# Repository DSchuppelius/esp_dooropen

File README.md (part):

# esp_dooropen

SIP-Türöffner für **ESP32 DevKit (WROOM-32)**, **WT32-ETH01** (ESP32 mit Ethernet) oder
**ESP8266 HW-364A** (NodeMCU mit fest verbautem OLED). Klingelt es, ruft der ESP per SIP ein Telefon an; mit **`*`** (oder einem Code) am
Telefon, über die **Weboberfläche**, per **Taster** oder aus **Home Assistant** wird die
Tür geöffnet.

Die Zielplattform wird über die PlatformIO-Umgebung gewählt (siehe
[Bauen & Flashen](#bauen--flashen-platformio)); der Code passt sich per
Präprozessor-Weiche automatisch an.

## Funktionen

- **Klingel-Eingang** (potentialfreier Kontakt, entprellt) mit Zähler und Hinweis
  „Es klingelt!“ im Web, auf dem Display und in Home Assistant.
- **Türsummer** über ein Relais, Dauer einstellbar (1–30 s). Ein Hardware-Timer
  schaltet das Relais auch dann pünktlich ab, wenn das Programm gerade hängt.
- **SIP-Anruf beim Klingeln** (getestet mit Asterisk, REGISTER mit Digest-Auth
  inkl. `qop=auth`/`opaque`, auch LANCOM-kompatibel):
  - **Rufkette**: mehrere Nummern nacheinander (z. B. `100, 101`), bis jemand abhebt,
  - nach dem Abheben ein Piepton im Hörer (G.711 A-law/µ-law), danach ein kurzer
    Piep alle 3 s, solange die Leitung offen ist,
  - **`*` am Telefon** (DTMF per RFC 4733 oder SIP INFO) öffnet die Tür und legt auf –
    oder ein **Öffnen-Code** (z. B. `1234`); dafür bleibt das Gespräch 30 s offen,
  - wird nicht abgehoben, wird der Anruf nach 15 s per `CANCEL` zurückgezogen,
  - **SIP-Status im Klartext** und Ergebnis des letzten Anrufs,
  - **robust im WLAN**: `INVITE` (auch mit Digest), `CANCEL`, `BYE` und `REGISTER`
    werden bei Paketverlust wiederholt (RFC 3261); eine gescheiterte Erneuerung
    meldet erst „abgemeldet“, wenn die Anmeldung wirklich abläuft. Kopfzeilen in
    jeder Schreibweise und Kurzform (`i:`, `f:` …) werden verstanden; ein Server als
    Hostname wird einmal je Anmeldung aufgelöst (folgt auch einem DHCP-Wechsel).
- **Klingeln per Anruf**: Eine TK-Anlage (z. B. OpenCom) ruft beim Klingeln den
  Türöffner an – er nimmt nicht ab und wertet das als Klingeln. Ganz ohne Verdrahtung.
- **Anrufe an den Türöffner** (optional): Wer die Nebenstelle des Türöffners anruft,
  hört einen kurzen Ton und tippt den Öffnen-Code oder einen **Gästecode**
  (bis zu 5, mit Name, Ablaufdatum und „einmalig“). Nach mehreren falschen Codes
  werden Anrufe für 15 min gesperrt.
- **Weboberfläche** mit hellem/dunklem Design, großem Öffnen-Knopf mit
  Countdown-Ring, Statuskacheln, Test-Anruf und Ton-Benachrichtigung im Browser.
- **Home Assistant** per MQTT mit Auto-Discovery (Schloss, Button, Klingel-Ereignis,
  Sensoren, letztes Ereignis, Einstellungen).
- **OLED SSD1306** (optional) zeigt IP, Signal- und Summer-Status; wird kein
  Display gefunden, läuft alles ohne.
- **Status-LED** mit Blinkmustern (Summer, WLAN-Einrichtung, kein WLAN, SIP fehlt).
- **Taster** vor Ort: Klingel-Taster (wirkt wie Klingeln) und Summer-Taster (öffnet).
- **Zweites Relais** (Tor, Garage, zweite Tür) mit eigenem Knopf, eigener Dauer und
  wahlweise auch für den Tür-Zugang.
- **Tastenfeld / RFID-Leser** (Wiegand, ESP32): Öffnen-Code oder Gästecode am
  Tastenfeld, Karten/Chips mit Namen; Sperre nach Fehlversuchen.
- **Telegram-Bot** (ESP32): Klingel-Mitteilung mit Knopf **„Öffnen“**, Befehle
  `/status` und `/oeffnen` – auch unterwegs, ohne Portfreigabe.
- **Apple Home** (HomeKit, eigene ESP32-Variante): Türschloss mit Türklingel direkt in
  der Home-App, ohne Home Assistant.
- **Zugänge** mit eigener Anmeldeseite: Admin (alles) und Tür-Zugang (nur öffnen und
  Verlauf sehen, z. B. für den Kunden; ohne Tür-Passwort ist die Tür offen), dazu bis
  zu 8 **weitere Benutzer** mit Rolle und Zeitfenster – der Verlauf zeigt, wer
  geöffnet hat. Ohne Admin-Passwort warnt die Oberfläche deutlich.
- **Firmware-Update über WLAN**: per Browser-Upload oder aus PlatformIO (OTA, nur
  mit Admin-Passwort).
- **Erreichbar unter `http://tueroeffner.local`** (mDNS).
- **Verlauf** der letzten 30 Ereignisse mit Uhrzeit (NTP) und Detail (z. B. Name des
  Gästecodes, Nummer des Anrufers, Benutzer); **übersteht Neustarts**. Dazu ein langer
  Verlauf (mehrere Tausend Einträge) im Flash, als **CSV** herunterladbar.
- **Nachtruhe**: in einem Zeitfenster beim Klingeln nicht anrufen.
- **Praxis-Modus**: an gewählten Wochentagen in **zwei Zeitfenstern** öffnet Klingeln
  die Tür automatisch (ohne Anruf); **gesetzliche Feiertage je Bundesland** werden
  automatisch berücksichtigt, weitere **Ausnahmetage** (Urlaub) einstellbar. Bei
  Fenstern über Mitternacht (z. B. 22–2 Uhr) gehört der Teil nach Mitternacht zum
  Vortag (Wochentag, Feier- und Ausnahmetag des Vortags).
- **Uhrzeit** per NTP: `pool.ntp.org`, ersatzweise das **Gateway** (Router oder
  TK-Anlage, z. B. FRITZ!Box „Zeitserver im Heimnetz bereitstellen“) und
  `de.pool.ntp.org`. So laufen Praxis-Modus, Nachtruhe und Zeitfenster auch ohne
  Internet, wenn der Router NTP anbietet. Ohne gültige Uhrzeit sind Praxis-Modus und
  Nachtruhe aus.
- **Türkontakt** (Reed): Tür offen/zu im Web und in Home Assistant, Meldung, wenn die
  Tür zu lange offen steht, und Prüfung, ob nach dem Summer wirklich jemand
  hereinkam („Tür nach Summer geöffnet“ / „Summer, Tür blieb zu“).
- **Push-Mitteilungen ohne Home Assistant** über **ntfy** oder **Telegram**
  (Klingeln, Öffnen, Tür zu lange offen, Sperre nach falschen Codes).
- **Syslog**: Meldungen und Ereignisse an einen Syslog-Server (Fehlersuche aus der Ferne).
- **Ethernet** statt WLAN mit dem WT32-ETH01 (z. B. per PoE versorgt).
- **Selbstheilung**: Ist das WLAN weg, verbindet der ESP jede Minute neu; als letzte
  Stufe Neustart nach 30 min. Ethernet: Neustart nur, wenn ein Link da ist, aber
  10 min keine IP kommt (bei gezogenem Kabel nicht). Außerdem Neustart, wenn der
  Speicher knapp oder zerstückelt ist oder das Programm hängt (Watchdog auf beiden
  Boards); der Grund des letzten Starts wird angezeigt.
- **Neue IP per DHCP** wird erkannt, SIP meldet sich dann sofort neu an.
- **Sicherung**: alle Einstellungen als Datei herunterladen und wieder einspielen.
- **Feste IP-Adresse** wahlweise statt DHCP (vor dem Speichern geprüft: Maske,
  Gateway im selben Netz, keine Netz-/Broadcast-Adresse – gegen Aussperren).
- **Sperre gegen Sturmklingeln**: Klingeln innerhalb von 5 s löst keinen neuen
  Anruf aus.
- **WiFiManager**: Ohne gespeicherte Zugangsdaten öffnet der ESP das
  passwortgeschützte WLAN `Tueroeffner-Setup` zum Eintragen – **ohne zu blockieren**:
  Klingel, Taster und Summer funktionieren währenddessen weiter. Ist das bekannte WLAN
  nur weg (z. B. startet der Router nach einem Stromausfall langsamer als der ESP),
  verbindet er weiter und öffnet die Einrichtung erst nach 15 min ohne Verbindung –
  dann für 5 min, während die Verbindung zum WLAN weiter versucht wird.
- Einstellungen, Zähler und Verlauf liegen im **LittleFS** (Zähler/Verlauf werden
  höchstens alle 5 min geschrieben, der lange Verlauf gebündelt höchstens einmal pro
  Minute, um den Flash zu schonen; vor Neustart und Update wird alles gesichert).
  Gespeichert wird geprüft über eine Hilfsdatei – bei vollem oder defektem Speicher
  bleibt die alte Datei, die Oberfläche meldet den Fehler. Für die Einstellungen bleibt
  immer Platz frei (notfalls wird der ältere Verlauf gelöscht). Wurde der Speicher beim
  Start formatiert oder ist er nicht verfügbar, zeigt die Oberfläche eine Warnung.
  Ereignisse ohne Uhrzeit (kein NTP) bleiben erhalten und erscheinen als „ohne Uhrzeit“.

## Verdrahtung

### ESP32 DevKit (WROOM-32)

Hier gelten echte GPIO-Nummern. Ein OLED ist optional.

| Funktion             | Pin      | Hinweis                                  |
|----------------------|----------|------------------------------------------|
| Relais S (Signal)    | GPIO26   | schaltet das Relais (active-high)        |
| Relais + / -         | 5V / GND | Relais-Modul aus 5 V versorgen           |
| Klingel-Kontakt      | GPIO27   | eine Ader hier, andere Ader an GND       |
| Klingel-Taster       | GPIO32   | Taster gegen GND, wirkt wie Klingeln     |
| Summer-Taster        | GPIO33   | Taster gegen GND, öffnet die Tür         |
| Türkontakt (optional)| GPIO25   | Reed-Kontakt gegen GND, geschlossen = zu |
| Status-LED           | GPIO2    | onboard oder extern, siehe [Status-LED](#status-led) |
| OLED SDA (optional)  | GPIO21   | nur falls ein Display genutzt wird       |
| OLED SCL (optional)  | GPIO22   | nur falls ein Display genutzt wird       |
| Relais 2 (optional)  | GPIO13   | zweites Relais (Tor, Garage …)           |
| Wiegand D0 (optional)| GPIO18   | Tastenfeld/RFID-Leser, siehe unten       |
| Wiegand D1 (optional)| GPIO19   | Tastenfeld/RFID-Leser, siehe unten       |

### ESP8266 HW-364A

Das OLED ist auf dem HW-364A **fest verdrahtet** an D5/D6.

| Funktion            | Pin         | Hinweis                                  |
|---------------------|-------------|------------------------------------------|
| OLED SDA (onboard)  | D5 (GPIO14) | fest verbaut, nicht belegen              |
| OLED SCL (onboard)  | D6 (GPIO12) | fest verbaut, nicht belegen              |
| KY-019 S (Signal)   | D1 (GPIO5)  | schaltet das Relais (active-high)        |
| KY-019 + (VCC)      | 5V / VU     | 5 V vom USB-Pin (nicht 3V3!)             |
| KY-019 - (GND)      | G           | gemeinsame Masse                         |
| Klingel-Kontakt     | D2 (GPIO4)  | eine Ader hier, andere Ader an GND       |
| Klingel-Taster      | D7 (GPIO13) | Taster gegen GND, wirkt wie Klingeln     |
| Summer-Taster       | D3 (GPIO0)  | gegen GND; Boot-Pin, nicht beim Start    |
| Türkontakt (opt.)   | RX (GPIO3)  | Reed gegen GND; beim USB-Flashen offen   |
| Relais 2 (opt.)     | D0 (GPIO16) | zweites Relais (Tor, Garage …)           |

Tastenfeld/RFID (Wiegand) gibt es auf dem ESP8266 nicht – dafür sind keine Pins frei.

**Summer-Taster an D3 (GPIO0):** GPIO0 entscheidet beim Start, ob der ESP8266 normal
startet oder auf eine neue Firmware wartet. Ist der Taster beim Einschalten **oder bei
einem Neustart** (Update, Selbstheilung, Watchdog) gedrückt – oder klemmt er bzw. ist
die Leitung feucht –, bleibt der ESP im Flash-Modus hängen, bis er stromlos war. Die
Firmware kann das nicht abfangen. Für Dauerbetrieb daher ESP32 bzw. die Steuerplatine
nutzen oder den Taster so montieren, dass er nicht klemmen kann.

### WT32-ETH01 (Ethernet)

Umgebung `wt32-eth01`. Netzwerk über das eingebaute LAN8720 (kein WLAN, keine
WLAN-Einrichtung; feste IP wie gewohnt in der Weboberfläche). IO35/IO36/IO39 sind
reine Eingänge **ohne** internen Pull-up.

| Funktion             | Pin   | Hinweis                                       |
|----------------------|-------|-----------------------------------------------|
| Relais (Summer)      | IO4   | active-high                                   |
| Klingel-Kontakt      | IO32  | gegen GND                                     |
| Klingel-Taster       | IO33  | gegen GND                                     |
| Summer-Taster        | IO12  | gegen GND (Strapping-Pin: nie auf 3,3 V ziehen) |
| Türkontakt           | IO2   | gegen GND                                     |
| Status-LED           | IO17  | LED mit 330 Ω gegen GND                        |
| Relais 2             | IO5   | Strapping-Pin, siehe Relais beim Start        |
| Wiegand D0 / D1      | IO35 / IO36 | Pull-up bzw. Pegelwandler nötig         |
| OLED SDA / SCL       | IO15 / IO14 | optional                                |

### Relais beim Start

Die Firmware setzt die Relais als allererstes in Ruhelage. Davor – während Reset,
Bootloader und Programmstart (einige 100 ms) – bestimmt die Hardware den Pegel:

| Board | Relais 2 | Pegel beim Start | Risiko |
| --- | --- | --- | --- |
| ESP32 DevKit / [Steuerplatine](hardware/README.md) | GPIO13 | kein Pull-up | keins (Platine: 100 kΩ hält das Gate auf GND) |
| WT32-ETH01 | IO5 | interner **Pull-up** (Strapping-Pin) | active-high-Modul kann kurz anziehen |
| ESP8266 | D0 (GPIO16) | beim Start **HIGH** | active-high-Modul kann kurz anziehen |

Relais 1 (Summer: GPIO26, IO4, D1/GPIO5) ist davon nicht betroffen. Hängt an Relais 2
etwas, das schon ein kurzer Impuls auslöst (Tor, Garage):

- **WT32-ETH01:** einen **Pull-down von 4,7–10 kΩ** vom Relais-Eingang (IN/S) nach GND
  einbauen – stärker als der interne Pull-up; IO5 darf beim Start LOW sein (betrifft
  nur das SDIO-Timing).
- **WT32-ETH01 und ESP8266:** ein Relais-Modul nehmen, das bei **LOW** schaltet, und in
  [src/config.h](src/config.h) `RELAY2_ACTIVE_LOW` auf `true` setzen – der HIGH-Pegel
  beim Start bedeutet dann „aus“.

### Tastenfeld / RFID-Leser (Wiegand)

Viele Zutritts-Tastenfelder und Kartenleser haben eine **Wiegand-Schnittstelle**
(Leitungen D0, D1, GND). Erkannt werden Tastendrücke (4 bzw. 8 Bit) und Karten
(26 Bit mit Parität, 34 Bit).

```text
Leser D0 (grün) ──[Pegelwandler]── GPIO18     Leser GND ── GND
Leser D1 (weiß) ──[Pegelwandler]── GPIO19     Leser +12 V ── eigenes Netzteil
```

Die meisten Leser ziehen D0/D1 auf **5 V** hoch – das verträgt der ESP32 nicht. Dann
einen **Pegelwandler** (z. B. BSS138-Modul) oder je Leitung einen Spannungsteiler
(z. B. 10 kΩ / 20 kΩ) dazwischen. Leser mit Open-Collector-Ausgang können direkt an
die Pins (der ESP schaltet den internen Pull-up ein).

Bedienung am Tastenfeld: Code eintippen, **#** bestätigt, ***** löscht. Gültig sind
Öffnen-Code und Gästecodes. Karten werden unter **Einstellungen → Tastenfeld / RFID**
angelernt: Karte an den Leser halten, die Nummer erscheint dort zum Übernehmen.

### Türöffner und Klingel

Der Türöffner hängt am **Relaiskontakt** (COM + NO) zusammen mit einem
**Klingeltrafo** (8–12 V AC): Trafo → COM, NO → Türöffner → zurück zum Trafo.

**Wichtig:**

- Der **Klingel-Eingang** verträgt nur einen *potentialfreien Kontakt* oder einen
  Optokoppler-Ausgang – **niemals die Klingelspannung direkt** (siehe
  [Klingel-Eingang anschließen](#klingel-eingang-anschließen)).
- Der **Summer** wird **nicht** vom ESP versorgt. Der ESP schaltet nur das Relais,
  der Summer hat seinen eigenen Stromkreis.
- Die Voreinstellung passt für das **KY-019** (schaltet bei HIGH). Für Relais-Module,
  die bei LOW schalten (viele blaue Module), in `src/config.h`
  `RELAY_ACTIVE_LOW` auf `true` setzen.

- **Zusätzliche Absicherung (empfohlen):** Das Relais wird per Hardware-Timer
  abgeschaltet, auch wenn das Programm hängt. Gegen einen *Defekt* des ESP (Pin bleibt
  auf HIGH) hilft das nicht. Wer das ausschließen will, schaltet den Türöffner über ein
  **Zeitrelais/Monoflop** (z. B. NE555-Schaltung oder fertiges „Delay Off“-Modul mit
  max. 30 s), das der ESP nur anstößt.

### Klingel-Eingang anschließen

Der Klingel-Eingang (ESP32: **GPIO27**, ESP8266: **D2**) arbeitet mit internem Pull-up:
**aktiv = gegen GND gezogen**. Erkannt werden sowohl Dauersignale als auch mit 50 Hz
pulsierende Signale (Optokoppler an Wechselspannung) – das Signal gilt als aktiv,
solange es in den letzten 40 ms aktiv war (`SIGNAL_AC_HOLD_MS`).

Gegen Störungen: Das Signal allein braucht mindestens 3 aktive Abtastungen
(`SIGNAL_MIN_SAMPLES`), und solange der Summer an ist sowie 300 ms danach zählt
Klingeln nicht (`RING_BUZZER_GUARD_MS`, Einkopplung vom Türöffner). Ein Eingang, der
schon beim Start aktiv ist (klemmender Taster, Feuchte), zählt erst, nachdem er einmal
frei war – das gilt auch für den Summer-Taster. Hängt das Programm kurz (Netzwerk,
Flash), erkennt ein Interrupt Tastendrücke ab 50 ms trotzdem und holt sie nach.

Welche Variante passt?

| Was ist vorhanden? | Variante |
| --- | --- |
| freier Schaltkontakt (Relaisausgang einer Sprechanlage, zweiter Kontakt am Taster) | **A** – direkt |
| klassische Klingel mit Klingeltrafo (8–12 V~) und Gong | **B** – Optokoppler parallel zum Gong |
| Klingeltaster an einer **TK-Anlage** (Sensor-Eingang, z. B. Aastra/Mitel OpenCom) | **C** – Optokoppler parallel zum Sensor |
| Klingel mit Gleichspannung (z. B. 12 V⎓) | **D** – Optokoppler, Polung beachten |
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
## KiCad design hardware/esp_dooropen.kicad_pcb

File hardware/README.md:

# Steuerplatine (KiCad)

KiCad-10-Projekt für eine eigene Platine mit ESP32-WROOM-32E. Die Pinbelegung entspricht dem ESP32-Zweig in [src/config.h](../src/config.h), es ist also keine Firmware-Änderung nötig.

| Datei | Inhalt |
| --- | --- |
| `esp_dooropen.kicad_pro` / `.kicad_sch` | KiCad-Projekt und Schaltplan |
| `schaltplan.pdf` | Schaltplan als PDF |
| `stueckliste.csv` | Stückliste, gruppiert nach Wert und Footprint |

Stand: nur der Schaltplan. Ein PCB-Layout gibt es noch nicht.

## Funktionsblöcke

- **Versorgung:** 12 V DC über Hohlstecker 5,5/2,1 oder Schraubklemme. Danach PTC 1,1 A, Verpolschutz SS34 und TVS-Diode SMBJ15CA. Ein RECOM R-78E5.0-1.0 erzeugt 5 V, ein AMS1117 daraus 3,3 V. USB-5V ist über eine Schottky-Diode entkoppelt, sodass USB und 12 V gleichzeitig angeschlossen sein dürfen.
- **USB-C:** CH340C mit Auto-Reset über DTR/RTS. Geflasht wird direkt per PlatformIO, ohne Tasten zu drücken. RESET und BOOT gibt es trotzdem als Taster.
- **Relais 1 und 2:** SRD-12VDC-SL-C mit 12-V-Spule, angesteuert über AO3400A mit Freilaufdiode und LED. Die Kontakte NO/COM/NC sind potentialfrei auf Schraubklemmen geführt.
- **Klingelsignal:** Zwei Varianten, beide verdrahtet. Sie wirken als ODER auf GPIO27 und brauchen keine Jumper.
  - Potentialfreier Kontakt an J4, Klemme 1 gegen GND.
  - 8–24 V AC oder DC an J5 über den Optokoppler LTV-814 (PC814). Der Optokoppler hat antiparallele LEDs, die Polarität ist also egal, und er trennt galvanisch. C11 überbrückt die Nulldurchgänge bei Wechselspannung.
- **Taster und Türkontakt:** Je 1 kΩ in Serie, 10 kΩ Pull-up und 100 nF gegen Störungen auf langen Leitungen.
- **Wiegand:** 12-V-Versorgung über PTC 200 mA. D0/D1 laufen über Schottky-Dioden BAT54W, daher sind 5-V-Leser ohne Pegelwandler erlaubt.
- **Erweiterungen:** OLED-Steckplatz (I2C, 3,3 V) und eine Erweiterungsleiste mit IO4, IO14, IO16 und IO17.

## Klemmenbelegung

| Klemme | Pins |
| --- | --- |
| J2 12 V | 1 +12 V, 2 GND |
| J4 Eingänge | 1 Klingel potentialfrei, 2 GND, 3 Klingeltaster, 4 Summertaster, 5 Türkontakt, 6 GND |
| J5 Klingel AC/DC | 1, 2 (8–24 V, beliebige Polarität) |
| J6 Wiegand | 1 +12 V, 2 GND, 3 D0, 4 D1 |
| J9 / J10 Relais | 1 NO, 2 COM, 3 NC |

## Zuordnung der GPIOs

| GPIO | Funktion |
| --- | --- |
| 26 | Relais 1 (Türsummer) |
| 13 | Relais 2 |
| 27 | Klingelsignal |
| 32 | Klingeltaster |
| 33 | Summertaster |
| 25 | Türkontakt |
| 18 / 19 | Wiegand D0 / D1 |
| 21 / 22 | I2C SDA / SCL |
| 2 | Status-LED |

## Hinweise

- **ERC:** Die einzige Meldung lautet „Power output an Power output“ zwischen CH340C-V3 und AMS1117. Das ist gewollt: Laut Datenblatt wird V3 bei 3,3-V-Betrieb mit VCC verbunden.
- **Nur Kleinspannung:** Die Platine ist für Kleinspannung ausgelegt (Klingeltrafo, Türöffner 8–24 V). Für 230 V an den Relaiskontakten fehlen die nötigen Luft- und Kriechstrecken.
- **Antenne:** Beim Layout muss die Antenne des WROOM-Moduls über den Platinenrand ragen. Darunter dürfen weder Kupfer noch Bauteile liegen.
- **Strapping-Pins:** GPIO12, GPIO15 und GPIO5 sind bewusst frei. GPIO0 und EN werden nur vom Auto-Reset und den Tastern benutzt.
- **Relais beim Start:** Die Relais hängen an GPIO26 und GPIO13 (keine Strapping-Pins, kein Pull-up beim Reset). R23 bzw. R25 (100 kΩ) halten die Gates von Q3/Q4 auf GND, solange der ESP32 startet – die Relais ziehen dabei nicht an. Bei Änderungen die Relais nicht auf GPIO5 oder GPIO15 legen (interner Pull-up beim Reset, siehe [README](../README.md#relais-beim-start)); diese Pull-downs nicht weglassen.

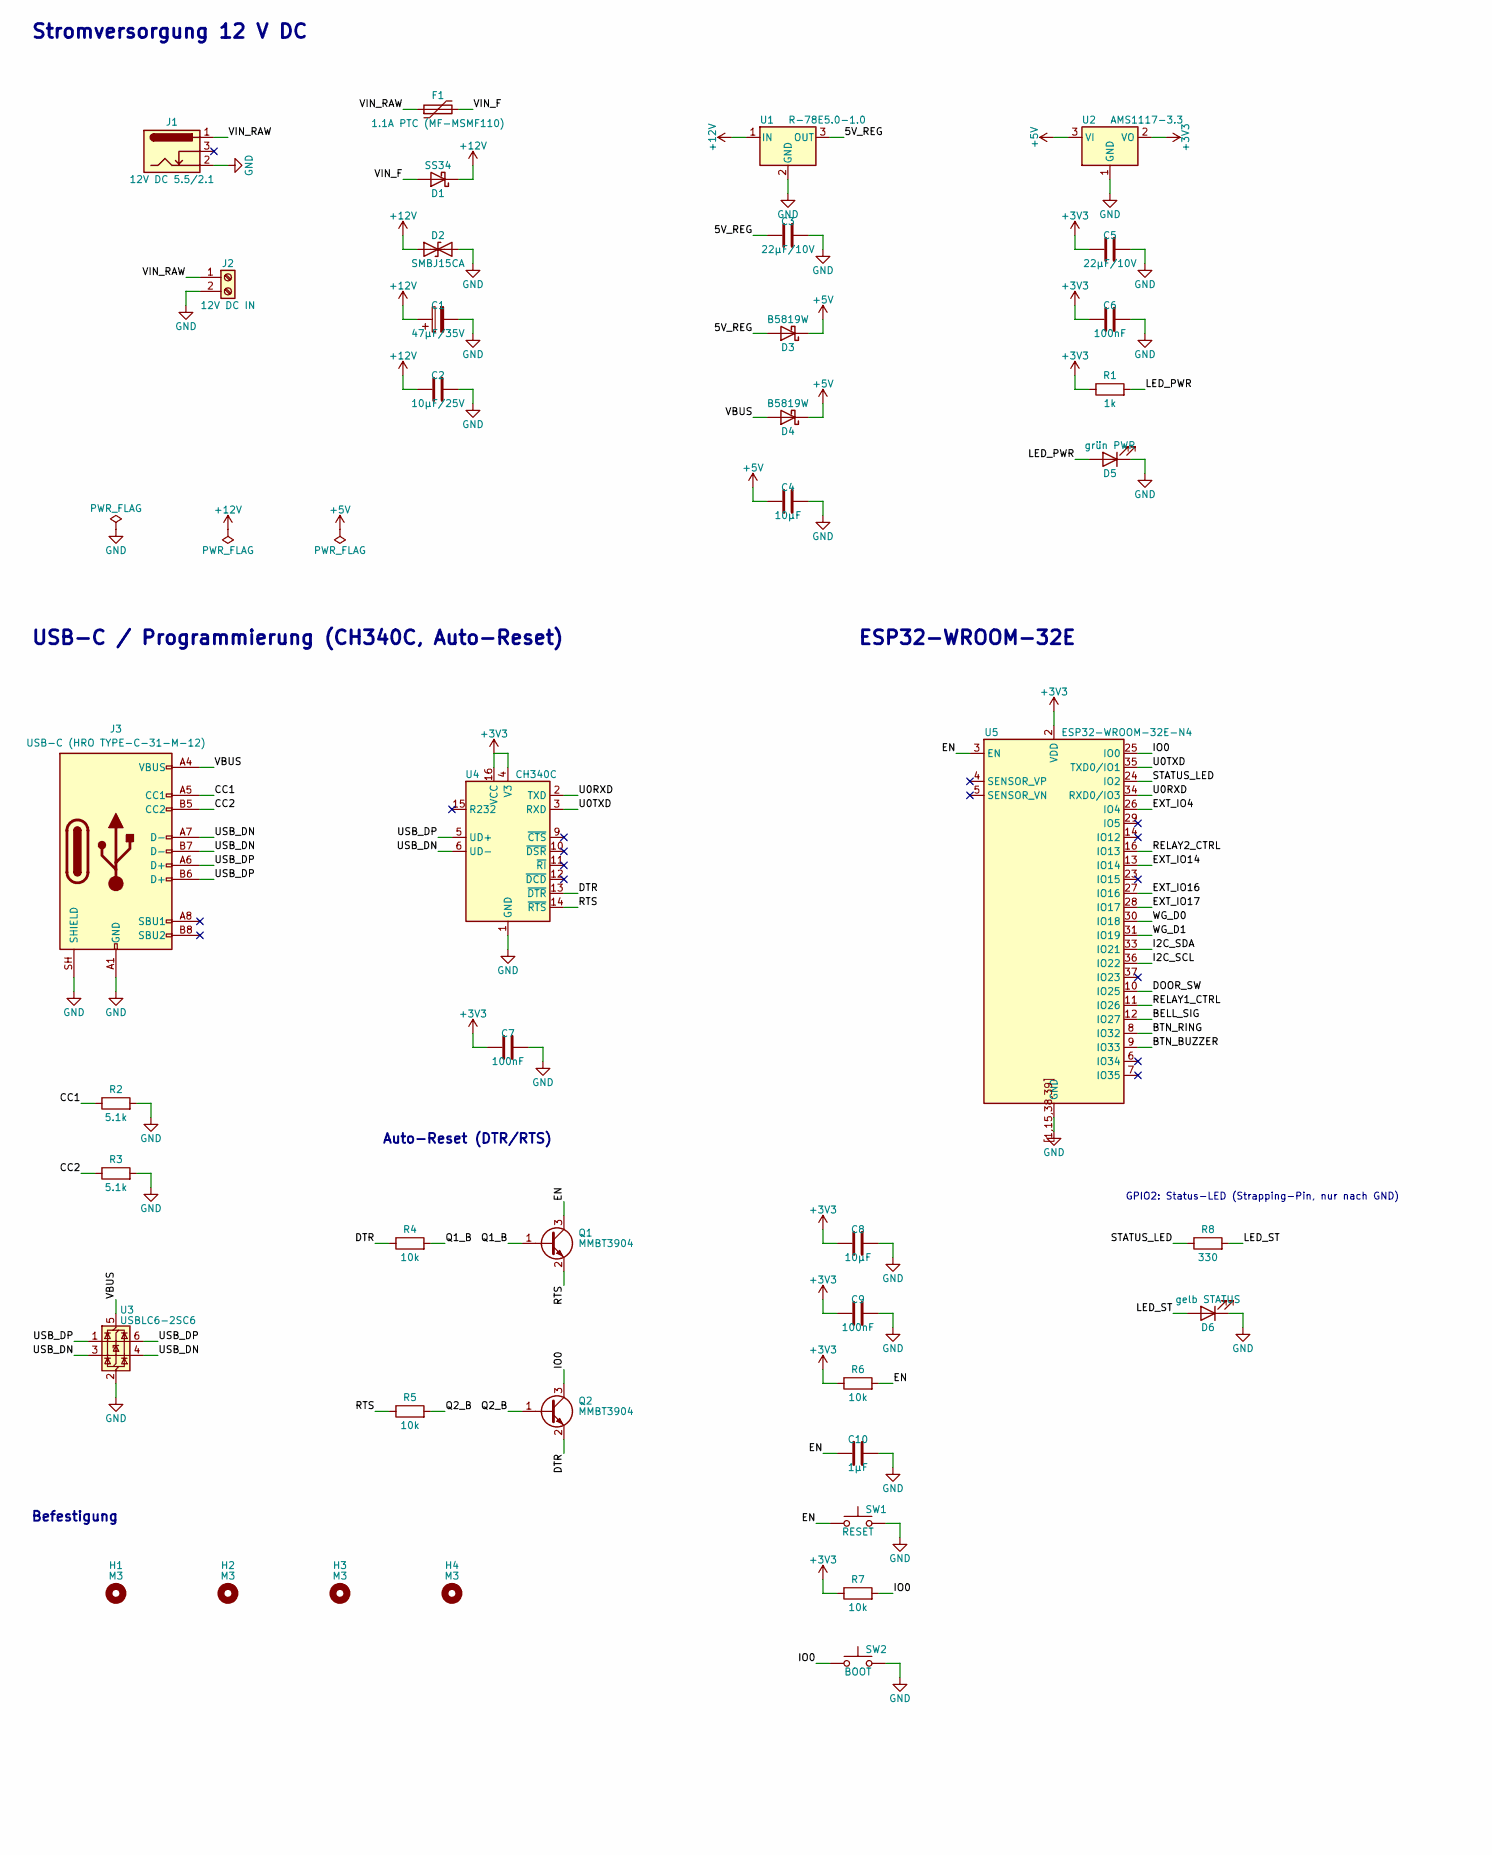
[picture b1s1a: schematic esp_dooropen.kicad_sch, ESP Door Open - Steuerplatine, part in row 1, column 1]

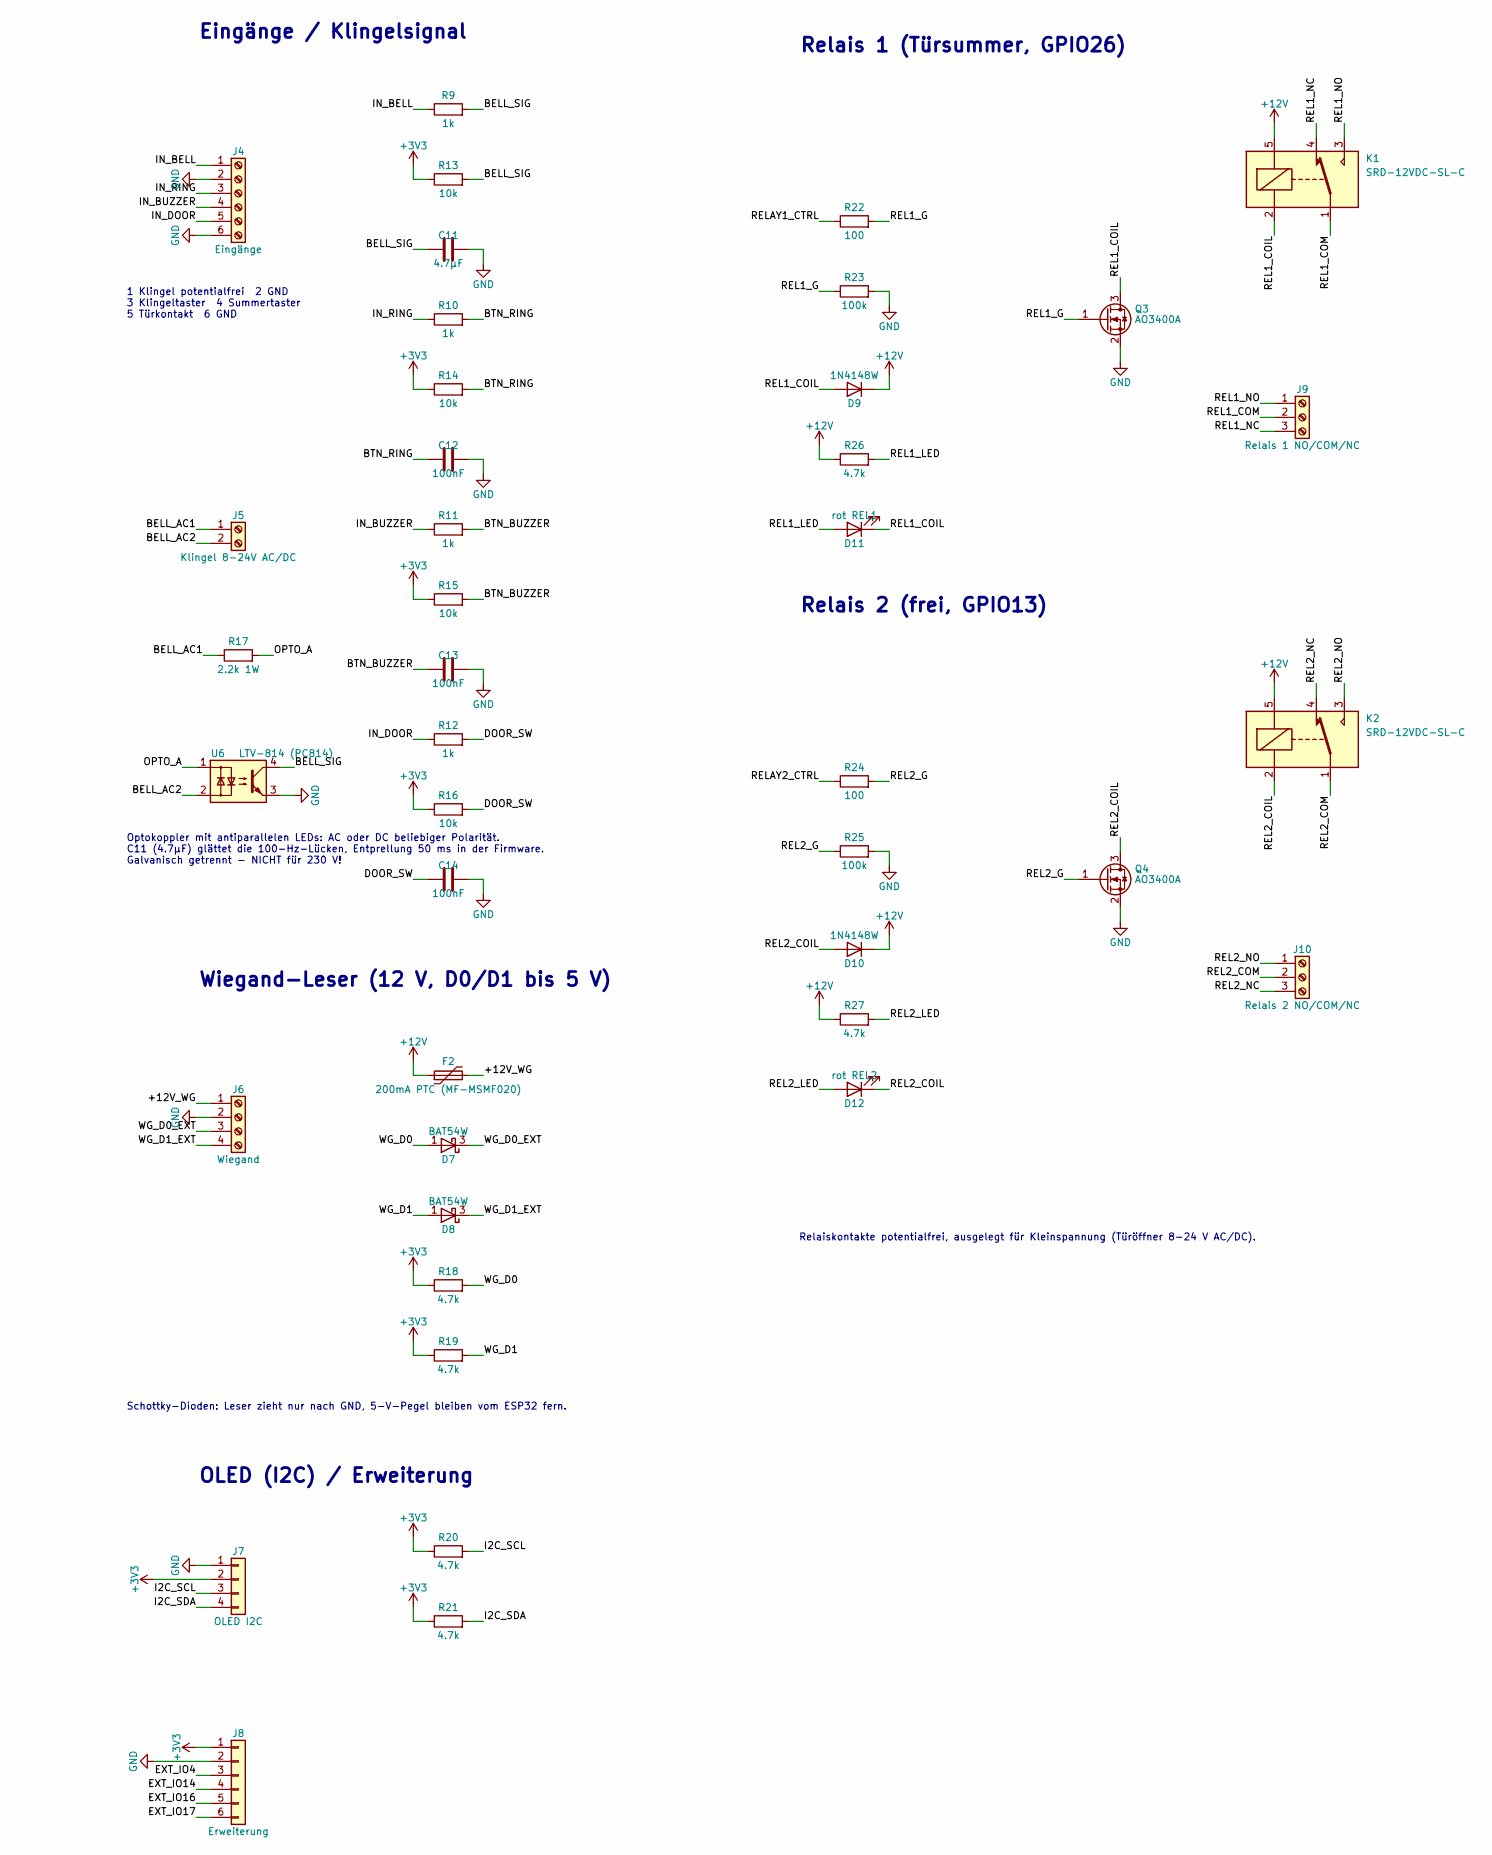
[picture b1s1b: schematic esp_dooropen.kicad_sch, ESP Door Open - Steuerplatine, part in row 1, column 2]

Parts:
C1: 47µF/35V; CP_Elec_6.3x7.7
C2: 10µF/25V; C_1206_3216Metric
C3, C5: 22µF/10V; C_1206_3216Metric
C4, C8: 10µF; C_0805_2012Metric
C6, C7, C9, C12, C13, C14: 100nF; C_0805_2012Metric
C10: 1µF; C_0805_2012Metric
C11: 4.7µF; C_0805_2012Metric
D1: SS34; D_SMA
D2: SMBJ15CA; D_SMB
D3, D4: B5819W; D_SOD-123
D5: grün PWR; LED_0805_2012Metric
D6: gelb STATUS; LED_0805_2012Metric
D7, D8: BAT54W; SOT-323_SC-70
D9, D10: 1N4148W; D_SOD-123
D11: rot REL1; LED_0805_2012Metric
D12: rot REL2; LED_0805_2012Metric
F1: 1.1A PTC (MF-MSMF110); Fuse_1812_4532Metric
F2: 200mA PTC (MF-MSMF020); Fuse_1206_3216Metric
H1, H2, H3, H4: M3; MountingHole_3.2mm_M3
J1: 12V DC 5.5/2.1; BarrelJack_Horizontal
J2: 12V DC IN; TerminalBlock_Phoenix_MKDS-1,5-2-5.08_1x02_P5.08mm_Horizont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
J3: USB-C (HRO TYPE-C-31-M-12); USB_C_Receptacle_HRO_TYPE-C-31-M-12
J4: Eingänge; TerminalBlock_Phoenix_MKDS-1,5-6-5.08_1x06_P5.08mm_Horizont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
J5: Klingel 8-24V AC/DC; TerminalBlock_Phoenix_MKDS-1,5-2-5.08_1x02_P5.08mm_Horizont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
J6: Wiegand; TerminalBlock_Phoenix_MKDS-1,5-4-5.08_1x04_P5.08mm_Horizont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
J7: OLED I2C; PinHeader_1x04_P2.54mm_Vertical
J8: Erweiterung; PinHeader_1x06_P2.54mm_Vertical
J9: Relais 1 NO/COM/NC; TerminalBlock_Phoenix_MKDS-1,5-3-5.08_1x03_P5.08mm_Horizont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
J10: Relais 2 NO/COM/NC; TerminalBlock_Phoenix_MKDS-1,5-3-5.08_1x03_P5.08mm_Horizont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
K1, K2: SRD-12VDC-SL-C; Relay_SPDT_SANYOU_SRD_Series_Form_C
Q1, Q2: MMBT3904; SOT-23
Q3, Q4: AO3400A; SOT-23
R1, R9, R10, R11, R12: 1k; R_0805_2012Metric
R2, R3: 5.1k; R_0805_2012Metric
R4, R5, R6, R7, R13, R14, R15, R16: 10k; R_0805_2012Metric
R8: 330; R_0805_2012Metric
R17: 2.2k 1W; R_Axial_DIN0414_L11.9mm_D4.5mm_P15.24mm_Horizontal
R18, R19, R20, R21, R26, R27: 4.7k; R_0805_2012Metric
R22, R24: 100; R_0805_2012Metric
R23, R25: 100k; R_0805_2012Metric
SW1: RESET; SW_SPST_TL3342
SW2: BOOT; SW_SPST_TL3342
U1: R-78E5.0-1.0; Converter_DCDC_RECOM_R-78E-0.5_THT
U2: AMS1117-3.3; SOT-223-3_TabPin2
U3: USBLC6-2SC6; SOT-23-6
U4: CH340C; SOIC-16_3.9x9.9mm_P1.27mm
U5: ESP32-WROOM-32E-N4; ESP32-WROOM-32E
U6: LTV-814 (PC814); DIP-4_W7.62mm

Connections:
+3V3: C5.1, C6.1, C7.1, C8.1, C9.1, J7.2, J8.1, R1.1, R6.1, R7.1, R13.1, R14.1, R15.1, R16.1, R18.1, R19.1, R20.1, R21.1, U2.2 (VO), U4.4 (V3), U4.16 (VCC), U5.2 (VDD)
+5V: C4.1, D3.1 (K), D4.1 (K), U2.3 (VI)
+12V: C1.1, C2.1, D1.1 (K), D2.1 (A1), D9.1 (K), D10.1 (K), F2.1, K1.5, K2.5, R26.1, R27.1, U1.1 (IN)
/5V_REG: C3.1, D3.2 (A), U1.3 (OUT)
/+12V_WG: F2.2, J6.1
/BELL_AC1: J5.1, R17.1
/BELL_AC2: J5.2, U6.2
/BELL_SIG: C11.1, R9.2, R13.2, U5.12 (IO27), U6.4
/BTN_BUZZER: C13.1, R11.2, R15.2, U5.9 (IO33)
/BTN_RING: C12.1, R10.2, R14.2, U5.8 (IO32)
/CC1: J3.A5 (CC1), R2.1
/CC2: J3.B5 (CC2), R3.1
/DOOR_SW: C14.1, R12.2, R16.2, U5.10 (IO25)
/DTR: Q2.2 (E), R4.1, U4.13 (~DTR)
/EN: C10.1, Q1.3 (C), R6.2, SW1.1, U5.3 (EN)
/EXT_IO4: J8.3, U5.26 (IO4)
/EXT_IO14: J8.4, U5.13 (IO14)
/EXT_IO16: J8.5, U5.27 (IO16)
/EXT_IO17: J8.6, U5.28 (IO17)
/I2C_SCL: J7.3, R20.2, U5.36 (IO22)
/I2C_SDA: J7.4, R21.2, U5.33 (IO21)
/IN_BELL: J4.1, R9.1
/IN_BUZZER: J4.4, R11.1
/IN_DOOR: J4.5, R12.1
/IN_RING: J4.3, R10.1
/IO0: Q2.3 (C), R7.2, SW2.1, U5.25 (IO0)
/LED_PWR: D5.2 (A), R1.2
/LED_ST: D6.2 (A), R8.2
/OPTO_A: R17.2, U6.1
/Q1_B: Q1.1 (B), R4.2
/Q2_B: Q2.1 (B), R5.2
/REL1_COIL: D9.2 (A), D11.1 (K), K1.2, Q3.3 (D)
/REL1_COM: J9.2, K1.1
/REL1_G: Q3.1 (G), R22.2, R23.1
/REL1_LED: D11.2 (A), R26.2
/REL1_NC: J9.3, K1.4
/REL1_NO: J9.1, K1.3
/REL2_COIL: D10.2 (A), D12.1 (K), K2.2, Q4.3 (D)
/REL2_COM: J10.2, K2.1
/REL2_G: Q4.1 (G), R24.2, R25.1
/REL2_LED: D12.2 (A), R27.2
/REL2_NC: J10.3, K2.4
/REL2_NO: J10.1, K2.3
/RELAY1_CTRL: R22.1, U5.11 (IO26)
/RELAY2_CTRL: R24.1, U5.16 (IO13)
/RTS: Q1.2 (E), R5.1, U4.14 (~RTS)
/STATUS_LED: R8.1, U5.24 (IO2)
/U0RXD: U4.2 (TXD), U5.34 (RXD0/IO3)
/U0TXD: U4.3 (RXD), U5.35 (TXD0/IO1)
/USB_DN: J3.A7 (D-), J3.B7 (D-), U3.3 (I/O2), U3.4 (I/O2), U4.6 (UD-)
/USB_DP: J3.A6 (D+), J3.B6 (D+), U3.1 (I/O1), U3.6 (I/O1), U4.5 (UD+)
/VBUS: D4.2 (A), J3.A4 (VBUS), J3.A9 (VBUS), J3.B4 (VBUS), J3.B9 (VBUS), U3.5 (VBUS)
/VIN_F: D1.2 (A), F1.2
/VIN_RAW: F1.1, J1.1, J2.1
/WG_D0: D7.1 (A), R18.2, U5.30 (IO18)
/WG_D0_EXT: D7.3 (K), J6.3
/WG_D1: D8.1 (A), R19.2, U5.31 (IO19)
/WG_D1_EXT: D8.3 (K), J6.4
GND: C1.2, C2.2, C3.2, C4.2, C5.2, C6.2, C7.2, C8.2, C9.2, C10.2, C11.2, C12.2, C13.2, C14.2, D2.2 (A2), D5.1 (K), D6.1 (K), J1.2, J2.2, J3.A1 (GND), J3.A12 (GND), J3.B1 (GND), J3.B12 (GND), J3.SH (SHIELD), J4.2, J4.6, J6.2, J7.1, J8.2, Q3.2 (S), Q4.2 (S), R2.2, R3.2, R23.2, R25.2, SW1.2, SW2.2, U1.2 (GND), U2.1 (GND), U3.2 (GND), U4.1 (GND), U5.1 (GND), U5.15 (GND), U5.38 (GND), U5.39 (GND), U5.[1,15,38,39] (GND), U6.3

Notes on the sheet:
Wiegand-Leser (12 V, D0/D1 bis 5 V)
Relais 2 (frei, GPIO13)
1 Klingel potentialfrei 2 GND 3 Klingeltaster 4 Summertaster 5 Türkontakt 6 GND
Optokoppler mit antiparallelen LEDs: AC oder DC beliebiger Polarität. C11 (4.7µF) glättet die 100-Hz-Lücken, Entprellung 50 ms in der Firmware. Galvanisch getrennt - NICHT für 230 V!
OLED (I2C) / Erweiterung
GPIO2: Status-LED (Strapping-Pin, nur nach GND)
Auto-Reset (DTR/RTS)
Stromversorgung 12 V DC
Befestigung
USB-C / Programmierung (CH340C, Auto-Reset)
Schottky-Dioden: Leser zieht nur nach GND, 5-V-Pegel bleiben vom ESP32 fern.
Relaiskontakte potentialfrei, ausgelegt für Kleinspannung (Türöffner 8-24 V AC/DC).
Eingänge / Klingelsignal
ESP32-WROOM-32E
Relais 1 (Türsummer, GPIO26)

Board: 2 copper layers, 83 parts (0 on the bottom side), 59 nets, no tracks yet.

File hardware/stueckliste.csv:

"Referenz","Wert","Footprint","Anzahl"
"C1","47µF/35V","Capacitor_SMD:CP_Elec_6.3x7.7","1"
"C2","10µF/25V","Capacitor_SMD:C_1206_3216Metric","1"
"C3,C5","22µF/10V","Capacitor_SMD:C_1206_3216Metric","2"
"C4,C8","10µF","Capacitor_SMD:C_0805_2012Metric","2"
"C6,C7,C9,C12,C13,C14","100nF","Capacitor_SMD:C_0805_2012Metric","6"
"C10","1µF","Capacitor_SMD:C_0805_2012Metric","1"
"C11","4.7µF","Capacitor_SMD:C_0805_2012Metric","1"
"D1","SS34","Diode_SMD:D_SMA","1"
"D2","SMBJ15CA","Diode_SMD:D_SMB","1"
"D3,D4","B5819W","Diode_SMD:D_SOD-123","2"
"D5","grün PWR","LED_SMD:LED_0805_2012Metric","1"
"D6","gelb STATUS","LED_SMD:LED_0805_2012Metric","1"
"D7,D8","BAT54W","Package_TO_SOT_SMD:SOT-323_SC-70","2"
"D9,D10","1N4148W","Diode_SMD:D_SOD-123","2"
"D11","rot REL1","LED_SMD:LED_0805_2012Metric","1"
"D12","rot REL2","LED_SMD:LED_0805_2012Metric","1"
"F1","1.1A PTC (MF-MSMF110)","Fuse:Fuse_1812_4532Metric","1"
"F2","200mA PTC (MF-MSMF020)","Fuse:Fuse_1206_3216Metric","1"
"H1,H2,H3,H4","M3","MountingHole:MountingHole_3.2mm_M3","4"
"J1","12V DC 5.5/2.1","Connector_BarrelJack:BarrelJack_Horizontal","1"
"J2","12V DC IN","TerminalBlock_Phoenix:TerminalBlock_Phoenix_MKDS-1,5-2-5.08_1x02_P5.08mm_Horizontal","1"
"J3","USB-C (HRO TYPE-C-31-M-12)","Connector_USB:USB_C_Receptacle_HRO_TYPE-C-31-M-12","1"
"J4","Eingänge","TerminalBlock_Phoenix:TerminalBlock_Phoenix_MKDS-1,5-6-5.08_1x06_P5.08mm_Horizontal","1"
"J5","Klingel 8-24V AC/DC","TerminalBlock_Phoenix:TerminalBlock_Phoenix_MKDS-1,5-2-5.08_1x02_P5.08mm_Horizontal","1"
"J6","Wiegand","TerminalBlock_Phoenix:TerminalBlock_Phoenix_MKDS-1,5-4-5.08_1x04_P5.08mm_Horizontal","1"
"J7","OLED I2C","Connector_PinHeader_2.54mm:PinHeader_1x04_P2.54mm_Vertical","1"
"J8","Erweiterung","Connector_PinHeader_2.54mm:PinHeader_1x06_P2.54mm_Vertical","1"
"J9","Relais 1 NO/COM/NC","TerminalBlock_Phoenix:TerminalBlock_Phoenix_MKDS-1,5-3-5.08_1x03_P5.08mm_Horizontal","1"
"J10","Relais 2 NO/COM/NC","TerminalBlock_Phoenix:TerminalBlock_Phoenix_MKDS-1,5-3-5.08_1x03_P5.08mm_Horizontal","1"
"K1,K2","SRD-12VDC-SL-C","Relay_THT:Relay_SPDT_SANYOU_SRD_Series_Form_C","2"
"Q1,Q2","MMBT3904","Package_TO_SOT_SMD:SOT-23","2"
"Q3,Q4","AO3400A","Package_TO_SOT_SMD:SOT-23","2"
"R1,R9,R10,R11,R12","1k","Resistor_SMD:R_0805_2012Metric","5"
"R2,R3","5.1k","Resistor_SMD:R_0805_2012Metric","2"
"R4,R5,R6,R7,R13,R14,R15,R16","10k","Resistor_SMD:R_0805_2012Metric","8"
"R8","330","Resistor_SMD:R_0805_2012Metric","1"
"R17","2.2k 1W","Resistor_THT:R_Axial_DIN0414_L11.9mm_D4.5mm_P15.24mm_Horizontal","1"
"R18,R19,R20,R21,R26,R27","4.7k","Resistor_SMD:R_0805_2012Metric","6"
"R22,R24","100","Resistor_SMD:R_0805_2012Metric","2"
"R23,R25","100k","Resistor_SMD:R_0805_2012Metric","2"
"SW1","RESET","Button_Switch_SMD:SW_SPST_TL3342","1"
"SW2","BOOT","Button_Switch_SMD:SW_SPST_TL3342","1"
"U1","R-78E5.0-1.0","Converter_DCDC:Converter_DCDC_RECOM_R-78E-0.5_THT","1"
"U2","AMS1117-3.3","Package_TO_SOT_SMD:SOT-223-3_TabPin2","1"
"U3","USBLC6-2SC6","Package_TO_SOT_SMD:SOT-23-6","1"
"U4","CH340C","Package_SO:SOIC-16_3.9x9.9mm_P1.27mm","1"
"U5","ESP32-WROOM-32E-N4","RF_Module:ESP32-WROOM-32E","1"
"U6","LTV-814 (PC814)","Package_DIP:DIP-4_W7.62mm","1"

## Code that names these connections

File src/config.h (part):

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#define RELAY_ACTIVE_LOW  false
#define PIN_SIGNAL     32   // Klingel-Kontakt gegen GND
#define SIGNAL_ACTIVE_LOW true
#define PIN_BTN_RING   33   // Klingel-Taster gegen GND
#define PIN_BTN_BUZZER 12   // Summer-Taster gegen GND (Strapping-Pin: nie extern auf 3,3 V ziehen)
#define PIN_DOOR       2    // Tuerkontakt gegen GND
#define PIN_STATUS_LED    17
#define STATUS_LED_ACTIVE_LOW false
// Zweites Relais und Tastenfeld/RFID (Wiegand) auf den reinen Eingaengen bzw. frei:
#define PIN_RELAY2     5    // RXD-Pin des Moduls (UART2), frei nutzbar
#define RELAY2_ACTIVE_LOW false
#define PIN_WG_D0      35   // Wiegand D0 (Pull-up/Pegelwandler noetig, siehe README)
#define PIN_WG_D1      36   // Wiegand D1

#elif defined(ESP32)
// ---- ESP32 DevKit (WROOM-32) --------------------------------
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#define SIGNAL_ACTIVE_LOW true

// Taster (je eine Ader an den Pin, die andere an GND; gedrueckt = LOW)
#define PIN_BTN_RING   32   // GPIO32: Klingel-Taster (wirkt wie das Klingelsignal)
#define PIN_BTN_BUZZER 33   // GPIO33: Summer-Taster (oeffnet die Tuer)
// Tuerkontakt (Reed-Kontakt gegen GND), im Web aktivieren
#define PIN_DOOR       25   // GPIO25

// Onboard-LED (GPIO2): Summer an = Dauerlicht, Blinkmuster zeigen WLAN-/SIP-Probleme.
// Manche DevKits haben dort keine LED (nur die rote Betriebs-LED) -> externe LED
// mit 330 Ohm von GPIO2 nach GND anschliessen.
#define PIN_STATUS_LED    2       // GPIO2 (Onboard-LED, active-high)
#define STATUS_LED_ACTIVE_LOW false

// Zweites Relais (z.B. Garage, zweite Tuer), im Web aktivieren
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
// Tastenfeld / RFID-Leser mit Wiegand-Schnittstelle (D0/D1), im Web aktivieren.
// Leser mit 5-V-Ausgaengen brauchen einen Pegelwandler (siehe README).
#define PIN_WG_D0      18   // GPIO18
#define PIN_WG_D1      19   // GPIO19

#else
// ---- ESP8266 HW-364A (NodeMCU mit fest verbautem OLED) -------
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#define SIGNAL_ACTIVE_LOW true

// Taster (je eine Ader an den Pin, die andere an GND; gedrueckt = LOW)
#define PIN_BTN_RING   D7   // GPIO13: Klingel-Taster (wirkt wie das Klingelsignal)
// GPIO0 ist Boot-Pin: beim Einschalten NICHT gedrueckt halten (sonst Flash-Modus)
#define PIN_BTN_BUZZER D3   // GPIO0:  Summer-Taster (oeffnet die Tuer)
// Tuerkontakt (Reed-Kontakt gegen GND) auf RX: die serielle Schnittstelle
// laeuft dann nur noch als Ausgabe. Beim Flashen per USB Kontakt offen lassen.
#define PIN_DOOR       3    // GPIO3 (RX)
#define DOOR_ON_RX_PIN

// Onboard-LED (blaue LED, GPIO2): Summer an = Dauerlicht, Blinkmuster fuer WLAN/SIP.
#define PIN_STATUS_LED    LED_BUILTIN
#define STATUS_LED_ACTIVE_LOW true

// Zweites Relais auf D0 (GPIO16). Tastenfeld/RFID (Wiegand) gibt es auf dem
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

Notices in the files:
README.md:
Dieses Projekt steht unter der [Apache License 2.0](LICENSE).
